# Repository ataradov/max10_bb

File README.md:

# Altera MAX 10 Breakout Board

This is a simple breakout board for Altera/Intel MAX 10 FPGAs.

This board is compatible with 10MxxSCE144yyy and 10MxxSAE144yyy (where xx >= 04).

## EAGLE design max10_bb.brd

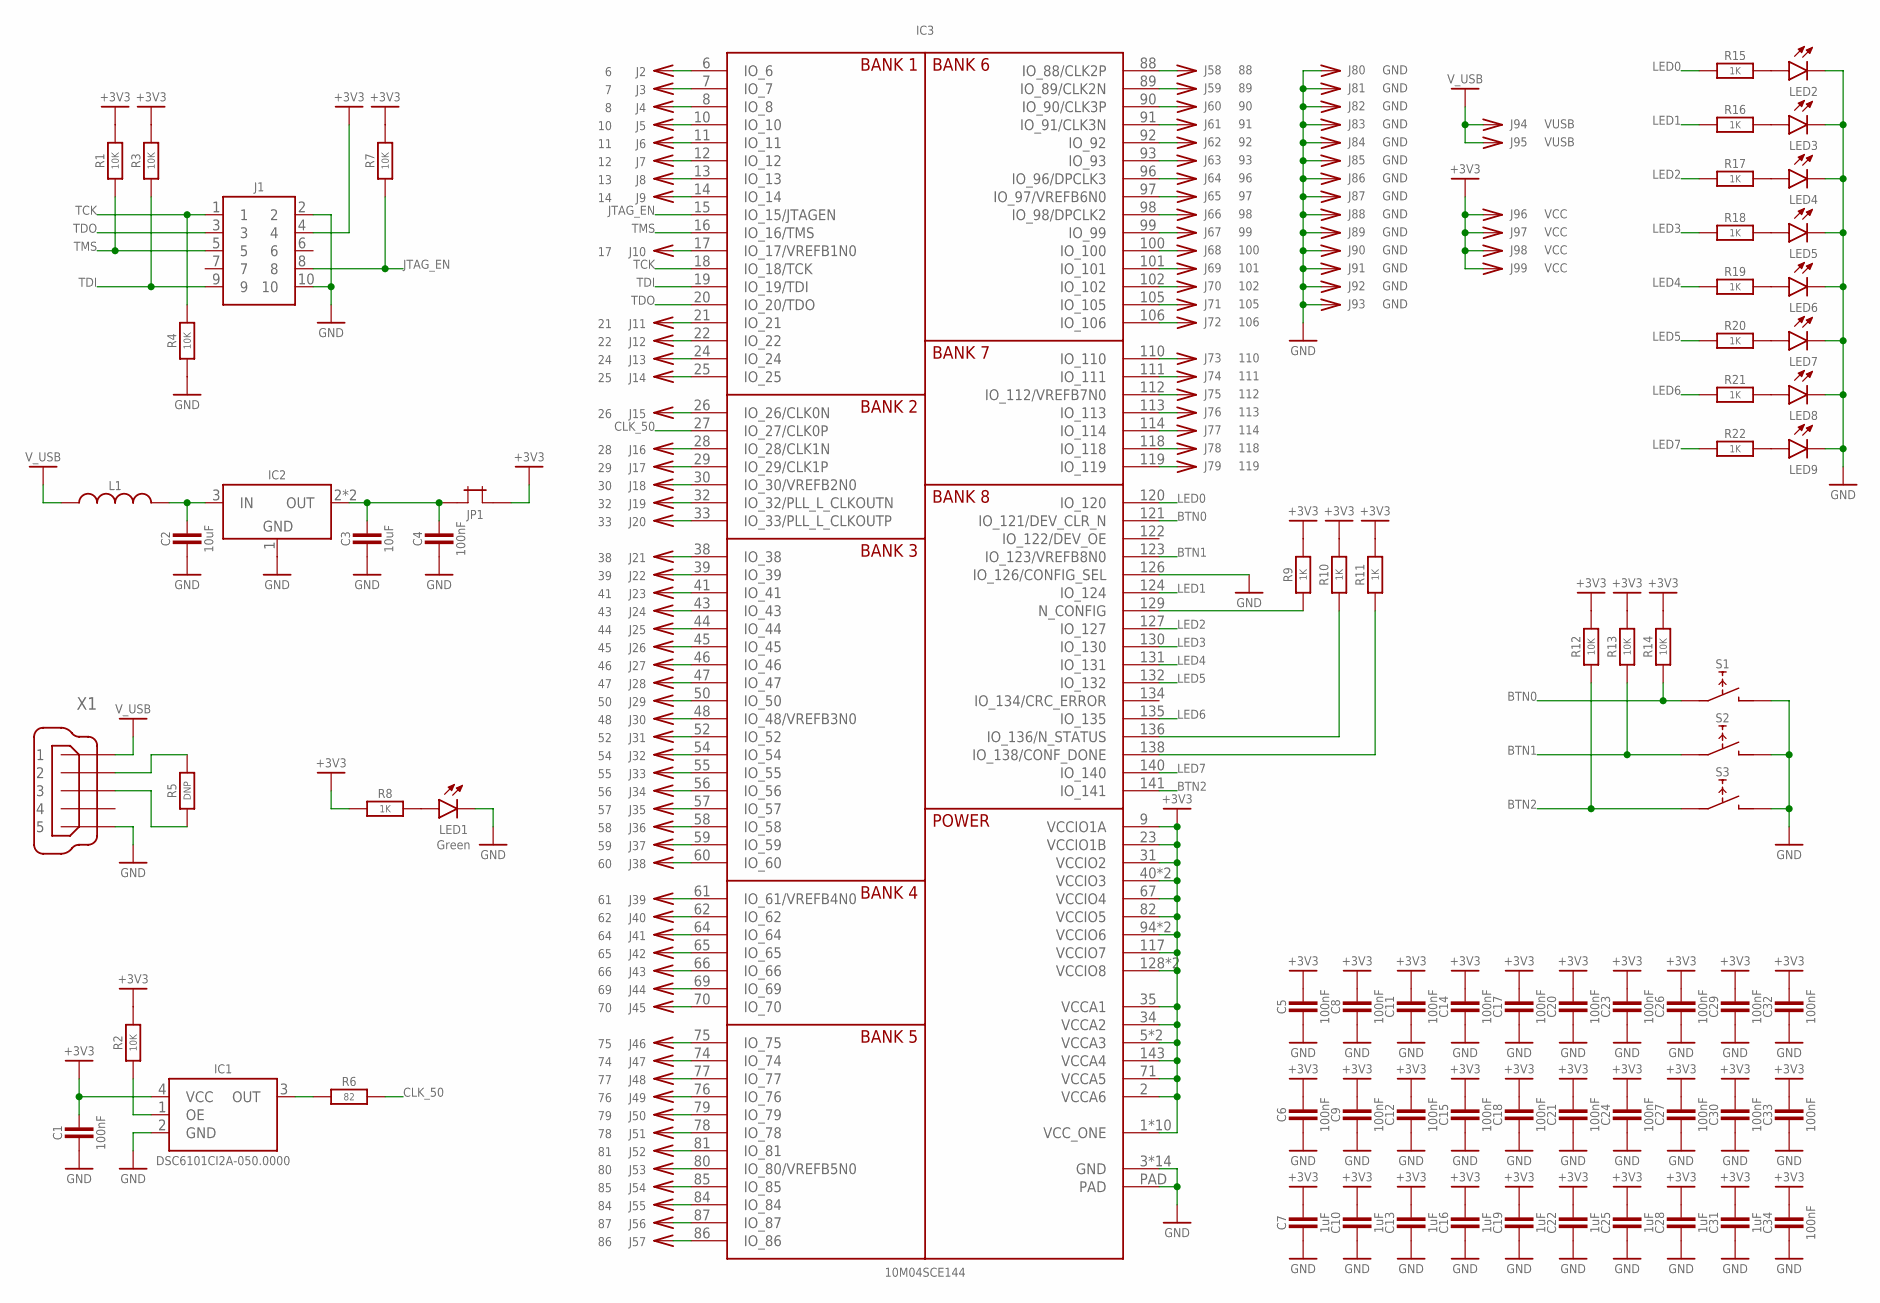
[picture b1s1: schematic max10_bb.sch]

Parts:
C1, C4, C5, C6, C8, C9, C11, C12, C14, C15, C17, C18, C20, C21, C23, C24, C26, C27, C29, C30, C32, C33, C34: 100nF; SMD0603
C2, C3: 10uF; SMD0805
C7, C10, C13, C16, C19, C22, C25, C28, C31: 1uF; SMD0603
IC1: DSC6101CI2A-050.0000; CDFN4
IC2: LM1117-SOT223; SOT223
IC3: 10M04SCE144; EQFP-144-0.5MM
J1: HEADER-5X2-TH-2.54; HEADER-5X2-2.54MM
J2: 6; PIN-TH
J3: 7; PIN-TH
J4: 8; PIN-TH
J5: 10; PIN-TH
J6: 11; PIN-TH
J7: 12; PIN-TH
J8: 13; PIN-TH
J9: 14; PIN-TH
J10: 17; PIN-TH
J11: 21; PIN-TH
J12: 22; PIN-TH
J13: 24; PIN-TH
J14: 25; PIN-TH
J15: 26; PIN-TH
J16: 28; PIN-TH
J17: 29; PIN-TH
J18: 30; PIN-TH
J19: 32; PIN-TH
J20: 33; PIN-TH
J21: 38; PIN-TH
J22: 39; PIN-TH
J23: 41; PIN-TH
J24: 43; PIN-TH
J25: 44; PIN-TH
J26: 45; PIN-TH
J27: 46; PIN-TH
J28: 47; PIN-TH
J29: 50; PIN-TH
J30: 48; PIN-TH
J31: 52; PIN-TH
J32: 54; PIN-TH
J33: 55; PIN-TH
J34: 56; PIN-TH
J35: 57; PIN-TH
J36: 58; PIN-TH
J37: 59; PIN-TH
J38: 60; PIN-TH
J39: 61; PIN-TH
J40: 62; PIN-TH
J41: 64; PIN-TH
J42: 65; PIN-TH
J43: 66; PIN-TH
J44: 69; PIN-TH
J45: 70; PIN-TH
J46: 75; PIN-TH
J47: 74; PIN-TH
J48: 77; PIN-TH
J49: 76; PIN-TH
J50: 79; PIN-TH
J51: 78; PIN-TH
J52: 81; PIN-TH
J53: 80; PIN-TH
J54: 85; PIN-TH
J55: 84; PIN-TH
J56: 87; PIN-TH
J57: 86; PIN-TH
J58: 88; PIN-TH
J59: 89; PIN-TH
J60: 90; PIN-TH
J61: 91; PIN-TH
J62: 92; PIN-TH
J63: 93; PIN-TH
J64: 96; PIN-TH
J65: 97; PIN-TH
J66: 98; PIN-TH
J67: 99; PIN-TH
J68: 100; PIN-TH
J69: 101; PIN-TH
J70: 102; PIN-TH
J71: 105; PIN-TH
J72: 106; PIN-TH
J73: 110; PIN-TH
J74: 111; PIN-TH
J75: 112; PIN-TH
J76: 113; PIN-TH
J77: 114; PIN-TH
J78: 118; PIN-TH
J79: 119; PIN-TH
J80, J81, J82, J83, J84, J85, J86, J87, J88, J89, J90, J91, J92, J93: GND; PIN-TH
J94, J95: VUSB; PIN-TH
J96, J97, J98, J99: VCC; PIN-TH
JP1: JUMPER-TH-TH; JUMPER-TH
L1: L-0603; SMD0603
LED1: Green; SMD0603
LED2, LED3, LED4, LED5, LED6, LED7, LED8, LED9: LED_SMDLED_0603; SMD0603
R1, R2, R3, R4, R7, R12, R13, R14: 10K; SMD0603
R5: DNP; SMD0603
R6: 82; SMD0603
R8, R9, R10, R11, R15, R16, R17, R18, R19, R20, R21, R22: 1K; SMD0603
S1, S2, S3: TACT_SWITCH_6MM-SMD; TACT-SMD-6MM
X1: MINI-USB-32005-201; 32005-201

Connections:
+3V3: C1.2, C5.2, C6.2, C7.2, C8.2, C9.2, C10.2, C11.2, C12.2, C13.2, C14.2, C15.2, C16.2, C17.2, C18.2, C19.2, C20.2, C21.2, C22.2, C23.2, C24.2, C25.2, C26.2, C27.2, C28.2, C29.2, C30.2, C31.2, C32.2, C33.2, C34.2, IC1.4 (VCC), IC3.1 (VCC_ONE), IC3.2 (VCCA6), IC3.5 (VCCA3), IC3.9 (VCCIO1A), IC3.23 (VCCIO1B), IC3.31 (VCCIO2), IC3.34 (VCCA2), IC3.35 (VCCA1), IC3.36 (VCC_ONE), IC3.37 (VCC_ONE), IC3.40 (VCCIO3), IC3.49 (VCCIO3), IC3.51 (VCC_ONE), IC3.67 (VCCIO4), IC3.71 (VCCA5), IC3.72 (VCC_ONE), IC3.73 (VCC_ONE), IC3.82 (VCCIO5), IC3.94 (VCCIO6), IC3.103 (VCCIO6), IC3.107 (VCCA3), IC3.108 (VCC_ONE), IC3.109 (VCC_ONE), IC3.115 (VCC_ONE), IC3.117 (VCCIO7), IC3.128 (VCCIO8), IC3.139 (VCCIO8), IC3.143 (VCCA4), IC3.144 (VCC_ONE), J1.4, J96.1, J97.1, J98.1, J99.1, JP1.2, R1.2, R2.2, R3.2, R7.2, R8.1, R9.2, R10.2, R11.2, R12.2, R13.2, R14.2
BTN0: IC3.121 (IO_121/DEV_CLR_N), R14.1, S1.1, S1.2 (1)
BTN1: IC3.123 (IO_123/VREFB8N0), R13.1, S2.1, S2.2 (1)
BTN2: IC3.141 (IO_141), R12.1, S3.1, S3.2 (1)
CLK_50: IC3.27 (IO_27/CLK0P), R6.2
GND: C1.1, C2.1, C3.1, C4.1, C5.1, C6.1, C7.1, C8.1, C9.1, C10.1, C11.1, C12.1, C13.1, C14.1, C15.1, C16.1, C17.1, C18.1, C19.1, C20.1, C21.1, C22.1, C23.1, C24.1, C25.1, C26.1, C27.1, C28.1, C29.1, C30.1, C31.1, C32.1, C33.1, C34.1, IC1.2 (GND), IC2.1 (GND), IC3.3 (GND), IC3.4 (GND), IC3.42 (GND), IC3.53 (GND), IC3.63 (GND), IC3.68 (GND), IC3.83 (GND), IC3.95 (GND), IC3.104 (GND), IC3.116 (GND), IC3.125 (GND), IC3.126 (IO_126/CONFIG_SEL), IC3.133 (GND), IC3.137 (GND), IC3.142 (GND), IC3.PAD, J1.2, J1.10, J80.1, J81.1, J82.1, J83.1, J84.1, J85.1, J86.1, J87.1, J88.1, J89.1, J90.1, J91.1, J92.1, J93.1, LED1.2 (C), LED2.2 (C), LED3.2 (C), LED4.2 (C), LED5.2 (C), LED6.2 (C), LED7.2 (C), LED8.2 (C), LED9.2 (C), R4.1, S1.3 (2), S1.4 (2), S2.3 (2), S2.4 (2), S3.3 (2), S3.4 (2), X1.5
IN: C2.2, IC2.3 (IN), L1.2
JTAG_EN: IC3.15 (IO_15/JTAGEN), J1.8, R7.1
LED0: IC3.120 (IO_120), R15.1
LED1: IC3.124 (IO_124), R16.1
LED2: IC3.127 (IO_127), R17.1
LED3: IC3.130 (IO_130), R18.1
LED4: IC3.131 (IO_131), R19.1
LED5: IC3.132 (IO_132), R20.1
LED6: IC3.135 (IO_135), R21.1
LED7: IC3.140 (IO_140), R22.1
unnamed: IC3.6 (IO_6), J2.1
unnamed: IC3.7 (IO_7), J3.1
unnamed: IC3.8 (IO_8), J4.1
unnamed: IC3.10 (IO_10), J5.1
unnamed: IC3.11 (IO_11), J6.1
unnamed: IC3.12 (IO_12), J7.1
unnamed: IC3.14 (IO_14), J9.1
unnamed: IC3.17 (IO_17/VREFB1N0), J10.1
unnamed: IC3.21 (IO_21), J11.1
unnamed: IC3.22 (IO_22), J12.1
unnamed: IC3.24 (IO_24), J13.1
unnamed: IC3.25 (IO_25), J14.1
unnamed: IC3.13 (IO_13), J8.1
unnamed: IC3.110 (IO_110), J73.1
unnamed: IC3.111 (IO_111), J74.1
unnamed: IC3.112 (IO_112/VREFB7N0), J75.1
unnamed: IC3.113 (IO_113), J76.1
unnamed: IC3.114 (IO_114), J77.1
unnamed: IC3.118 (IO_118), J78.1
unnamed: IC3.119 (IO_119), J79.1
unnamed: IC3.88 (IO_88/CLK2P), J58.1
unnamed: IC3.89 (IO_89/CLK2N), J59.1
unnamed: IC3.90 (IO_90/CLK3P), J60.1
unnamed: IC3.91 (IO_91/CLK3N), J61.1
unnamed: IC3.92 (IO_92), J62.1
unnamed: IC3.93 (IO_93), J63.1
unnamed: IC3.96 (IO_96/DPCLK3), J64.1
unnamed: IC3.97 (IO_97/VREFB6N0), J65.1
unnamed: IC3.98 (IO_98/DPCLK2), J66.1
unnamed: IC3.99 (IO_99), J67.1
unnamed: IC3.100 (IO_100), J68.1
unnamed: IC3.101 (IO_101), J69.1
unnamed: IC3.102 (IO_102), J70.1
unnamed: IC3.105 (IO_105), J71.1
unnamed: IC3.106 (IO_106), J72.1
unnamed: IC3.26 (IO_26/CLK0N), J15.1
unnamed: IC3.28 (IO_28/CLK1N), J16.1
unnamed: IC3.29 (IO_29/CLK1P), J17.1
unnamed: IC3.30 (IO_30/VREFB2N0), J18.1
unnamed: IC3.32 (IO_32/PLL_L_CLKOUTN), J19.1
unnamed: IC3.33 (IO_33/PLL_L_CLKOUTP), J20.1
unnamed: IC3.38 (IO_38), J21.1
unnamed: IC3.39 (IO_39), J22.1
unnamed: IC3.41 (IO_41), J23.1
unnamed: IC3.44 (IO_44), J25.1
unnamed: IC3.45 (IO_45), J26.1
unnamed: IC3.46 (IO_46), J27.1
unnamed: IC3.47 (IO_47), J28.1
unnamed: IC3.50 (IO_50), J29.1
unnamed: IC3.48 (IO_48/VREFB3N0), J30.1
unnamed: IC3.52 (IO_52), J31.1
unnamed: IC3.54 (IO_54), J32.1
unnamed: IC3.55 (IO_55), J33.1
unnamed: IC3.56 (IO_56), J34.1
unnamed: IC3.57 (IO_57), J35.1
unnamed: IC3.58 (IO_58), J36.1
unnamed: IC3.59 (IO_59), J37.1
unnamed: IC3.60 (IO_60), J38.1
unnamed: IC3.61 (IO_61/VREFB4N0), J39.1
unnamed: IC3.62 (IO_62), J40.1
unnamed: IC3.64 (IO_64), J41.1
unnamed: IC3.65 (IO_65), J42.1
unnamed: IC3.66 (IO_66), J43.1
unnamed: IC3.69 (IO_69), J44.1
unnamed: IC3.70 (IO_70), J45.1
unnamed: IC3.75 (IO_75), J46.1
unnamed: IC3.74 (IO_74), J47.1
unnamed: IC3.76 (IO_76), J49.1
unnamed: IC3.79 (IO_79), J50.1
unnamed: IC3.81 (IO_81), J52.1
unnamed: IC3.80 (IO_80/VREFB5N0), J53.1
unnamed: IC3.84 (IO_84), J55.1
unnamed: IC3.87 (IO_87), J56.1
unnamed: IC3.86 (IO_86), J57.1
unnamed: IC3.85 (IO_85), J54.1
unnamed: IC3.78 (IO_78), J51.1
unnamed: IC3.77 (IO_77), J48.1
unnamed: IC3.43 (IO_43), J24.1
unnamed: IC1.3 (OUT), R6.1
unnamed: R5.2, X1.2
unnamed: R5.1, X1.3
unnamed: IC1.1 (OE), R2.1
unnamed: LED1.1 (A), R8.2
unnamed: IC3.129 (N_CONFIG), R9.1
unnamed: IC3.136 (IO_136/N_STATUS), R10.1
unnamed: IC3.138 (IO_138/CONF_DONE), R11.1
unnamed: LED6.1 (A), R19.2
unnamed: LED7.1 (A), R20.2
unnamed: LED8.1 (A), R21.2
unnamed: LED9.1 (A), R22.2
unnamed: LED2.1 (A), R15.2
unnamed: LED3.1 (A), R16.2
unnamed: LED4.1 (A), R17.2
unnamed: LED5.1 (A), R18.2
OUT: C3.2, C4.2, IC2.2 (OUT), IC2.4 (OUT), JP1.1
TCK: IC3.18 (IO_18/TCK), J1.1, R4.2
TDI: IC3.19 (IO_19/TDI), J1.9, R3.1
TDO: IC3.20 (IO_20/TDO), J1.3
TMS: IC3.16 (IO_16/TMS), J1.5, R1.1
V_USB: J94.1, J95.1, L1.1, X1.1

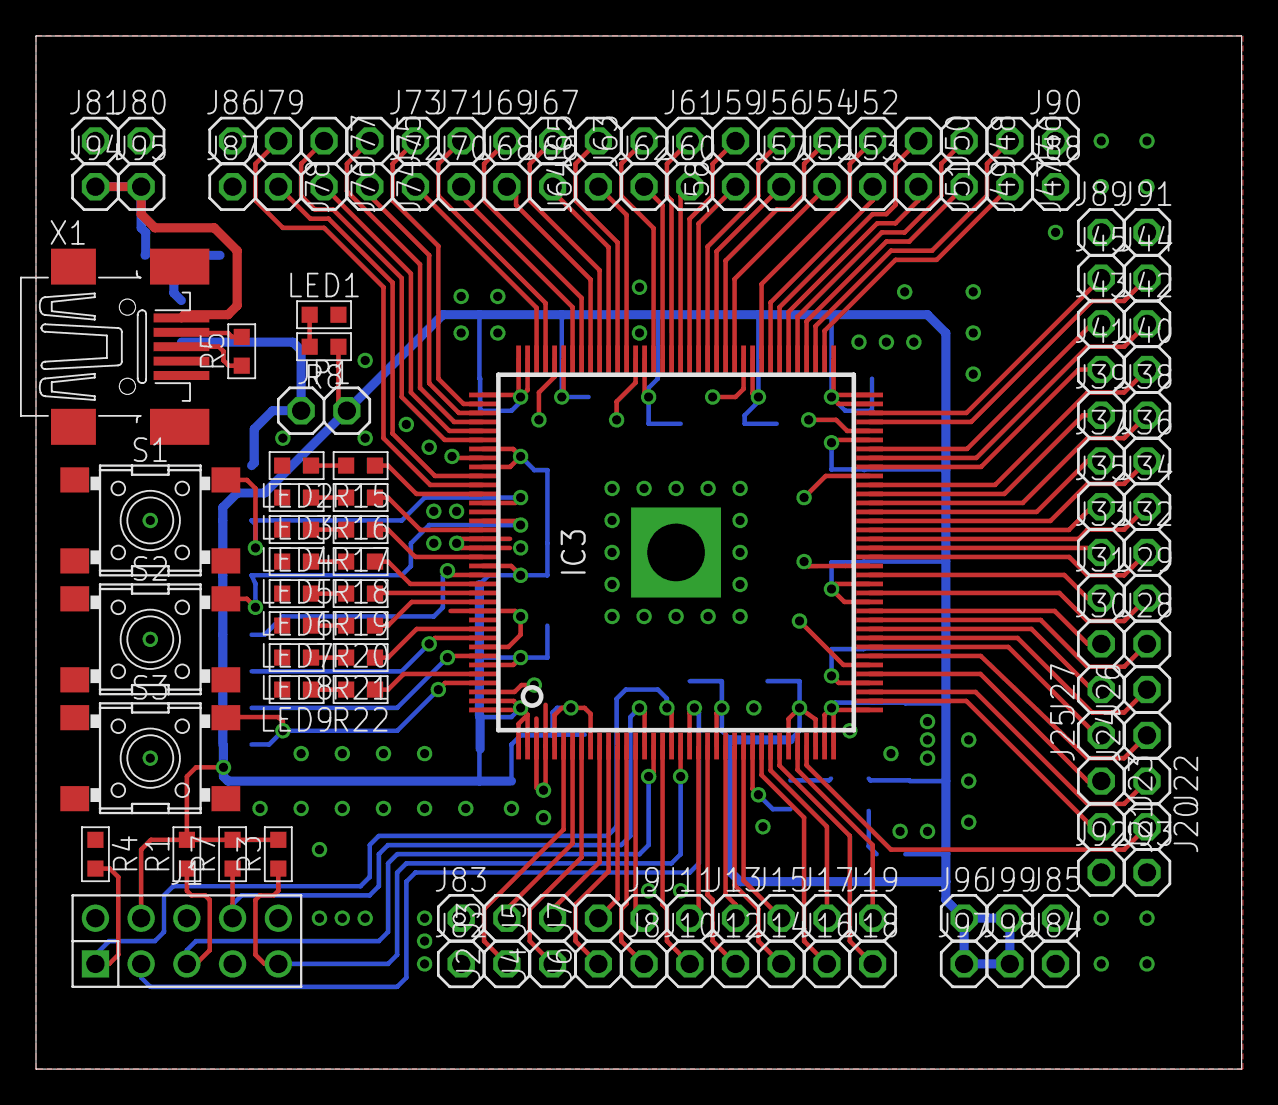
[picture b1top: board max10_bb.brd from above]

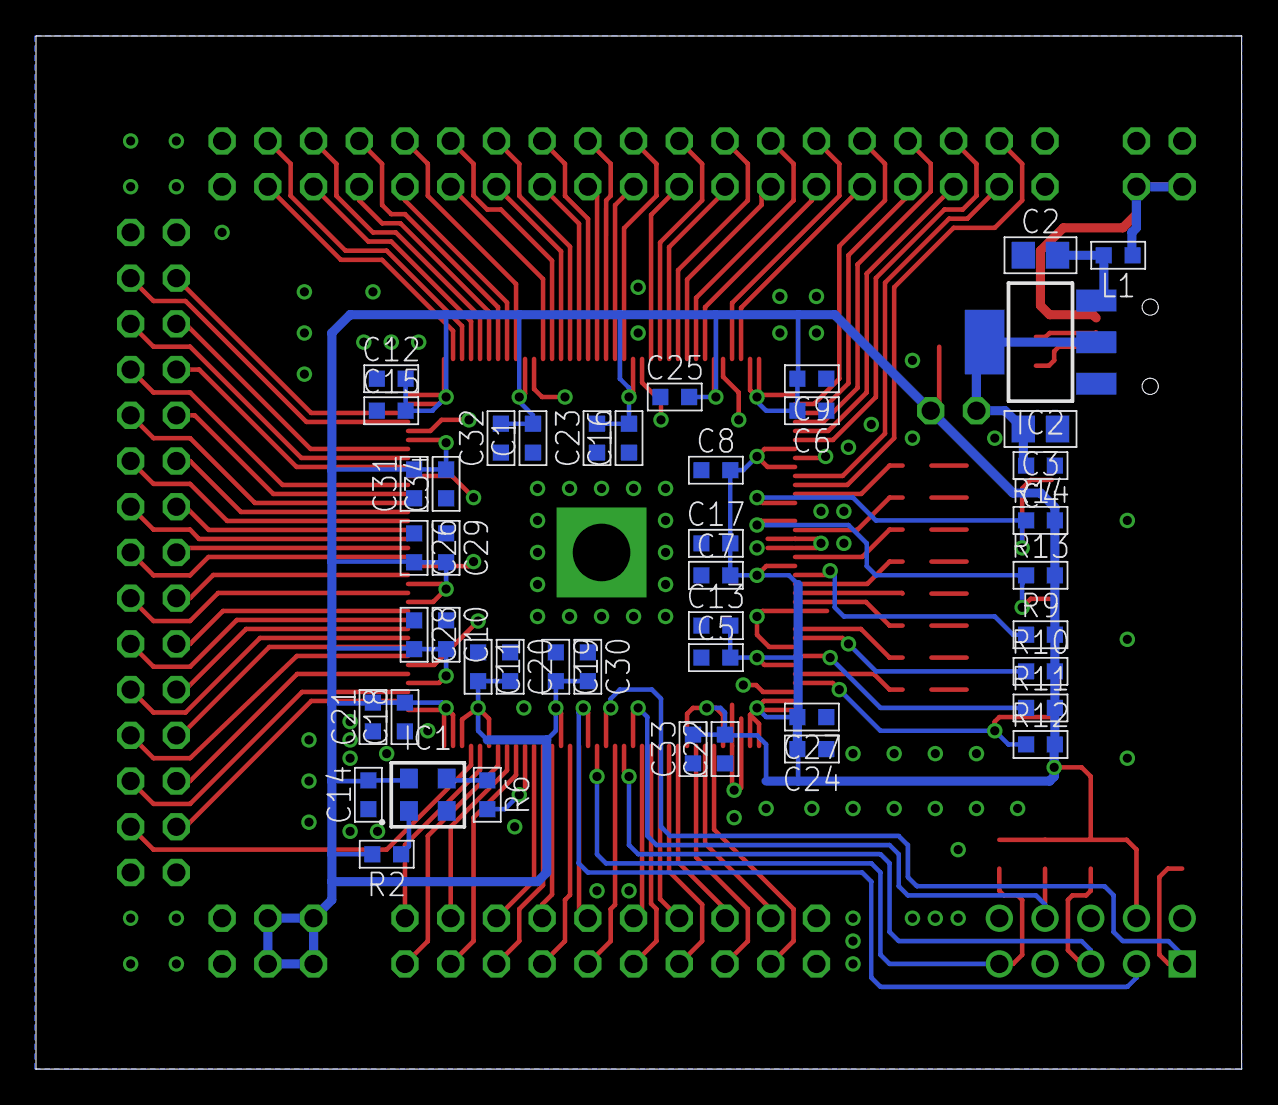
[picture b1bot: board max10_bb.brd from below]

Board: 2 copper layers, 67.0 x 57.4 mm, 173 parts (45 on the bottom side), 116 nets.

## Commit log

2018-01-12 Initial release
2018-03-26 Added a demo project
2018-03-26 Removed workspace file
